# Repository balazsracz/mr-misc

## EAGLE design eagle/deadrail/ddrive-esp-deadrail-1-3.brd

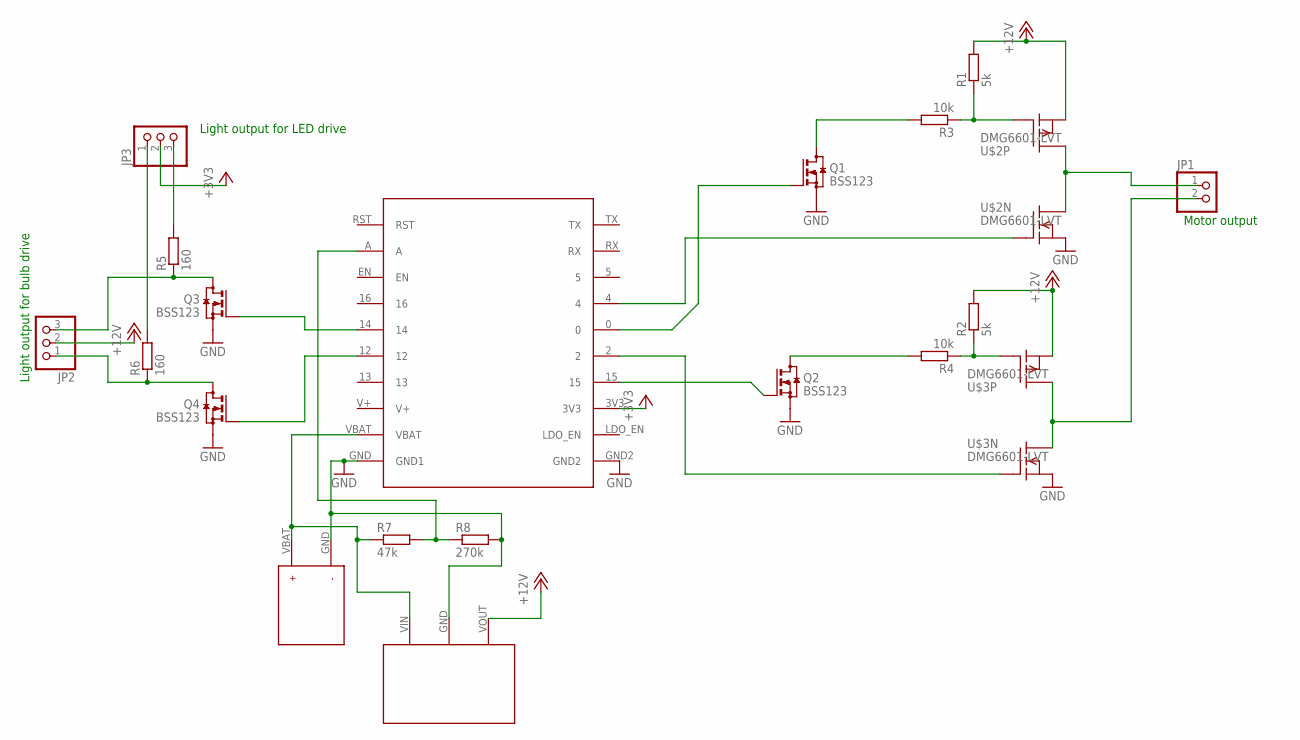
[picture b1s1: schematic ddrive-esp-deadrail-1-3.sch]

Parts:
JP1: PINHD-1X2; 1X02
JP2, JP3: PINHD-1X3; 1X03
Q1, Q2, Q3, Q4: BSS123; SOT23
R1, R2: 5k; R0805
R3, R4: 10k; R0805
R5, R6: 160; R0805
R7: 47k; R0805
R8: 270k; R0805
U$1: ESP12-HUZZAH
U$2, U$3: DMG6601-LVT; TSOT-26
U$4: JST-PINHD; JST-PINHDR
U$5: POLOLU-VREG12; POLOLU-REGULATOR

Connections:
+3V3: JP3.2, U$1.3V3
+12V: JP2.2, R1.2, R2.2, U$2.2 (S), U$3.2 (S), U$5.VOUT
GND: Q1.2 (S), Q2.2 (S), Q3.2 (S), Q4.2 (S), R8.2, U$1.GND (GND1), U$1.GND2, U$2.5 (S), U$3.5 (S), U$4.GND, U$5.GND
unnamed: JP1.1, U$2.4 (D), U$2.6 (D)
unnamed: R1.1, R3.1, U$2.3 (G)
unnamed: Q2.3 (D), R4.2
unnamed: R2.1, R4.1, U$3.3 (G)
unnamed: Q1.1 (G), U$1.0
unnamed: Q1.3 (D), R3.2
unnamed: JP1.2, U$3.4 (D), U$3.6 (D)
unnamed: U$1.4, U$2.1 (G)
unnamed: Q2.1 (G), U$1.15
unnamed: U$1.2, U$3.1 (G)
unnamed: Q3.1 (G), U$1.14
unnamed: Q4.1 (G), U$1.12
unnamed: JP2.3, Q3.3 (D), R5.1
unnamed: JP2.1, Q4.3 (D), R6.1
unnamed: JP3.3, R5.2
unnamed: JP3.1, R6.2
unnamed: R7.2, R8.1, U$1.A
V+: U$1.V+
VBAT: R7.1, U$1.VBAT, U$4.VBAT, U$5.VIN

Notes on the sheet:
Light output for LED drive
Light output for bulb drive
Motor output

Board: 2 copper layers, 20 parts (2 on the bottom side), 21 nets, no tracks yet.
